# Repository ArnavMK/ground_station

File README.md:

# Glacadóir: Handheld Rocketry Ground Station

**3D Render:**

**PCB Layout (Rev 1.2):**

### What is this project?

Glacadóir is a custom handheld telemetry terminal designed to receive, process, and visualize real-time data from high-power rockets. It serves as the primary interface for the **ULAS HiPR** team during the **Mach 2026** and **Euroc 2026** competition.

This board acts as a portable "command center," featuring:

- **Adafruit KB2040 (RP2040):** The brain handling high-speed data processing.
- **Radio expansion cartridges:** A game boy style cartridge system that enables the ground station to adapt to different radio protocols like UART (Eggfinder RX) and SPI (LoRa)
- **IPS Display:** Real-time visualization of flight curves and GPS coordinates.
- **Power Management:** A dual-input "Ideal Diode" with Micro Lipo battery charger system for seamless USB/Battery switching. (also data transfer).

### How to use it?

Glacadóir is designed for field portability. It connects to a standard 868MHz SMA antenna and is powered by a single-cell LiPo battery.

1. **Telemetry:** Receives flight data via the radio protocol attached and displays it on the internal IPS screen.
2. **Interaction:** A 5-button navigational matrix allows the user to switch between data screens (velocity, altitude, GPS).
3. **Expansion:** Features a dedicated UART/SPI expansion port to connect external modules like an Eggtimer or secondary radio adapters.
4. **Charging:** Integrated USB-C charging allows for field-topping while the station remains active.

### 3D enclosure cad
there is no proper enclosure cad yet, but it will be inspired by a gameboy and cartridge design like so

### Why I made it

This project was made for the ULAS HiPR’s ground station needs. 

---

### Bill of Materials (BOM) - Rev 1.2

| Part | Amount | Link | Cost |
| --- | --- | --- | --- |
| MicroLipo charger | 1 | [Link](https://www.digikey.ie/en/products/detail/adafruit-industries-llc/1904/5054545) | 6.95 |
| Display | 1 | [Link](https://www.digikey.ie/en/products/detail/adafruit-industries-llc/5206/15204095) | 17.5 |
| Main Power Switch | 1 | [Link](https://www.digikey.com/en/products/detail/c-k/OS102011MA1QN1/1981430) | 0.65 |
|  |  |  |  |
| Tactile Switches | 6 | [Link](https://www.digikey.com/en/products/detail/e-switch/TL3301AF160QG/378993) | 0.39 |
| SP0503BAHT ESD diode array | 1 | [Link](https://www.digikey.com/en/products/detail/littelfuse-inc/SP0503BAHTG/1154308) | 0.53 |
| 0805 resistor package (10k) | 11 | [Link](https://www.digikey.com/en/products/detail/bourns-inc/CR0805-FX-1002ELF/3593209) | 0.1 |
| 0805 resistor package (100K) | 2 | [Link](https://www.digikey.com/en/products/detail/bourns-inc/CR0805-FX-1003ELF/3740947) | 0.1 |
| 0805 resistor package (200K) | 1 | [Link](https://www.digikey.com/en/products/detail/bourns-inc/CR0805-FX-2003ELF/3784733) | 0.1 |
| 0805 capacitor package (0.1uF) | 4 | [Link](https://www.digikey.com/en/products/detail/nextgen-components/0805B104K500BD/15776052) | 0.078 |
| 0805 capacitor package (10uF) | 1 | [Link](https://www.digikey.com/en/products/detail/nextgen-components/0805W106K250CC/18676983) | 0.17 |
| 0805 capacitor package (4.7uF) | 2 | [Link](https://www.digikey.com/en/products/detail/nextgen-components/0805B475K160CC/22601960?s=N4IgjCBcpgLFoDGUBmBDANgZwKYBoQB7KAbXAAYAOAdlgCYQBdAgBwBcoQBlNgJwEsAdgHMQAXwJhqCEMkjps%2BIqRD06sMAFYmrDpG58hoiSDqaG0Waky4CxSGXV0AnGEo6Q7TjwEjxk50pnGTkFW2UHEHImEzpyWGDLUJslezJyADowAAIAVoAxEAJYDOo8wslyco8vfQBVQX42AHkUAFkcNCwAV14cfxAAWngk60U7FVcANnJpRhNB7VH5FInIiHmxMSA) | 0.34 |
| Analog divices Ideal Diodes MAX40200 | 2 | [Link](https://www.digikey.ie/en/products/detail/analog-devices-inc-maxim-integrated/MAX40200AUK-T/7599791) | 1.89 |
| Female SMA connector | 1 | [Link](https://www.digikey.ie/en/products/detail/molex/0732511153/11305709) | 3.9 |
| Lora Module | 1 | [Link](https://www.digikey.com/en/products/detail/rf-solutions/RF-LORA-868-SO/5291460) | 20.16 |
| Eggfinder (already have it) | 1 | — | — |
| Radio adapter Female connector. (already have it) | 1 | — | — |
| KB2040 MCU | 1 | [Link](https://www.adafruit.com/product/5302) | 8.95 |
|  |  |  |  |
| **Total SUM** |  |  | **61.808** |

**Total Estimated Component Cost: ~€62.00** (Excluding shipping/PCBs)

### Key Technical Revisions (Rev 1.2)

- **Ideal Diode Logic:** Swapped standard Schottky diodes for MAX40200 "Ideal" diodes to reclaim $500\text{mV}$ of battery headroom, ensuring stability deep into the discharge cycle.
- **RF Signal Integrity:** Implemented a $50\,\Omega$ coplanar waveguide ($0.1565\text{ mm}$ trace, $0.508\text{ mm}$ clearance) with via-fencing to maximize 868MHz range.
- **Expansion Logic:** Corrected the UART crossover (CBR_RX to RADIO_TX) to allow bi-directional communication with Eggtimer adapters.
- **Signal Cleanup:** Removed pull-up resistors on actively driven SPI lines (SCK/MOSI) to maintain sharp digital transitions at high clock speeds.

---

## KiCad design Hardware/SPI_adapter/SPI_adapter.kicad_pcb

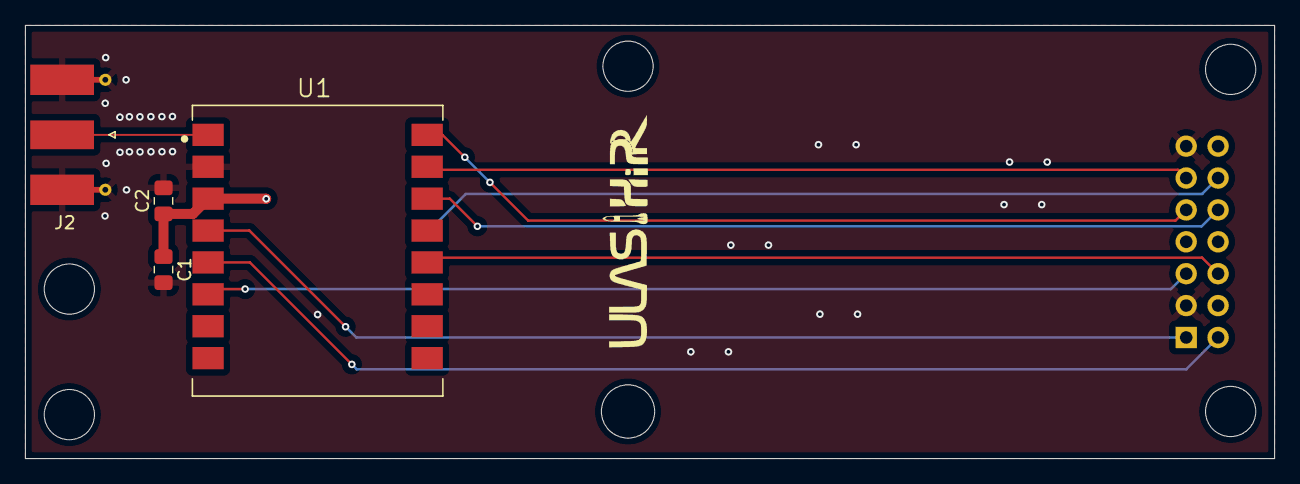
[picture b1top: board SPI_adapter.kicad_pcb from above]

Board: 4 copper layers, 99.5 x 34.5 mm, 5 parts (1 on the bottom side), 11 nets.

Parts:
C1: 100nF; C_0805_2012Metric_Pad1.18x1.45mm_HandSolder
C2: 4.7µF; C_0805_2012Metric_Pad1.18x1.45mm_HandSolder
J1: Conn_02x07_Top_Bottom; PinHeader_2x07_P2.54mm_Horizontal
J2: Conn_Coaxial; SMA_Molex_73251-1153_EdgeMount_Horizontal
U1: RF-LORA-868-SO; XCVR_RF-LORA-868-SO

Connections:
+3.3V: C1.1, C2.1, J1.14, U1.3 (VCC)
/RADIO_DIO1: J1.5, U1.6 (DIO0)
/RADIO_RST: J1.6, U1.12 (RESET)
/RF_ANT: J2.1 (In), U1.1 (ANT)
/RX_SWITCH: J1.1, U1.4 (RX_SWITCH)
/SPI_CS: J1.9, U1.16 (~SEL)
/SPI_MISO: J1.10, U1.14 (SDO)
/SPI_MOSI: J1.11, U1.15 (SDI)
/SPI_SCK: J1.12, U1.13 (SCLK)
/TX_SWITCH: J1.2, U1.5 (TX_SWITCH)
GND: C1.2, C2.2, J1.3, J1.13, J2.2 (Ext), U1.2 (GND)

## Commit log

2026-03-23 Project commit
2026-03-23 read me rev 1
    *you will find the bom.csv in the root directory* added to the README.
2026-03-23 Update README.md for project introduction
2026-03-23 images
2026-03-23 Update README with additional project screenshots
    Added multiple screenshots to the README for better visualization of the project, including 3D renders and PCB layouts.
2026-03-23 Add 3D enclosure CAD section to README
    Added section about 3D enclosure CAD inspired by Gameboy design.
2026-03-23 Fix image link format for 3D CAD enclosure
    Updated image syntax for 3D enclosure CAD in README.
